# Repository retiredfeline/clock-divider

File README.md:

# Small clock divider board

These are the Kicad design files for a CD4060 based [small clock divider](https://hackaday.io/project/202239-small-clock-divider).

## Notes

A crystal (up to about 1.5 MHz) can be used, or an external clock source can be connected. A solder jumper enables the latter.

One of the divisor outputs can be routed with a solder jumper to drive the output transistor which is open collector.

## Authors

* **Ken Yap**

## License

See the [LICENSE](LICENSE.md) file for license rights and limitations (MIT).

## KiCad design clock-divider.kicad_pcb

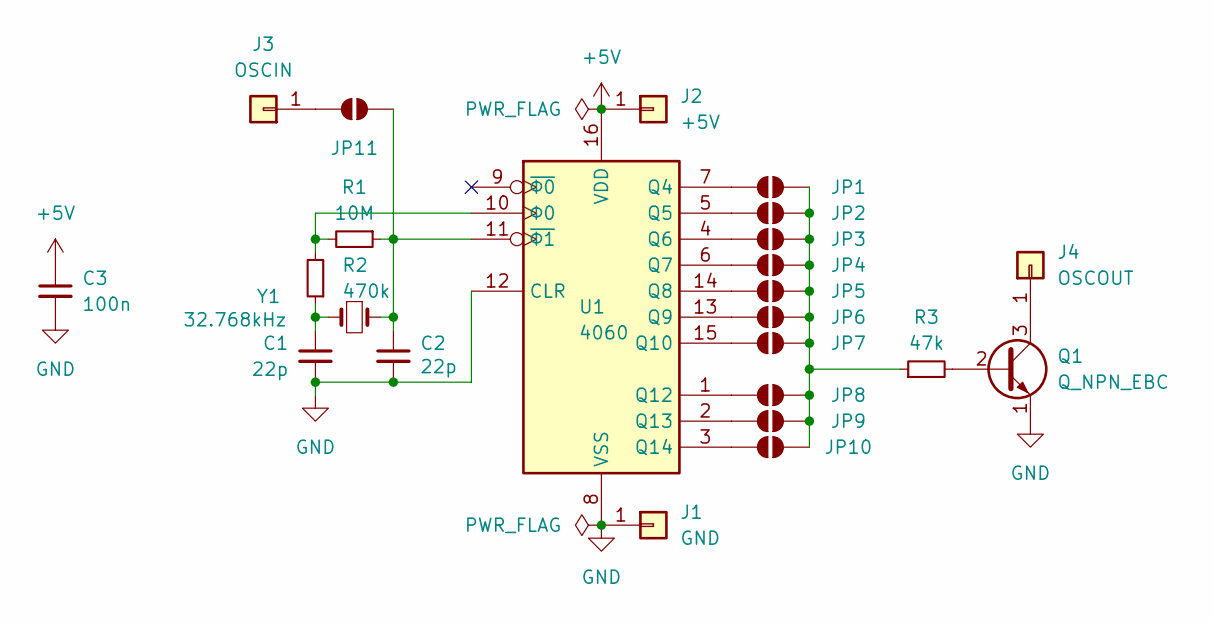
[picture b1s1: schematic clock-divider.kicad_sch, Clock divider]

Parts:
C1, C2: 22p; C_Disc_D3.0mm_W1.6mm_P2.50mm
C3: 100n; C_Disc_D3.0mm_W1.6mm_P2.50mm
J1: GND; SolderWire-0.1sqmm_1x01_D0.4mm_OD1mm
J2: +5V; SolderWire-0.1sqmm_1x01_D0.4mm_OD1mm
J3: OSCIN; SolderWire-0.1sqmm_1x01_D0.4mm_OD1mm
J4: OSCOUT; SolderWire-0.1sqmm_1x01_D0.4mm_OD1mm
JP1, JP2, JP3, JP4, JP5, JP6, JP7, JP8, JP9, JP10, JP11: SolderJumper_2_Open; SolderJumper-2_P1.3mm_Open_TrianglePad1.0x1.5mm
Q1: Q_NPN_EBC; TO-92L_Inline_Wide
R1: 10M; R_Axial_DIN0309_L9.0mm_D3.2mm_P2.54mm_Vertical
R2: 470k; R_Axial_DIN0309_L9.0mm_D3.2mm_P2.54mm_Vertical
R3: 47k; R_Axial_DIN0309_L9.0mm_D3.2mm_P2.54mm_Vertical
U1: 4060; DIP-16_W7.62mm
Y1: 32.768kHz; Crystal_C38-LF_D3.0mm_L8.0mm_Vertical_Extra_Pad

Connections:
+5V: C3.1, J2.1, U1.16 (VDD)
GND: C1.2, C2.2, C3.2, J1.1, Q1.1 (E), U1.8 (VSS), U1.12 (CLR)
unnamed: C1.1, R2.1, Y1.2
unnamed: J3.1, JP11.1 (A)
unnamed: J4.1, Q1.3 (C)
unnamed: JP1.1 (A), U1.7 (Q4)
unnamed: JP1.2 (B), JP2.2 (B), JP3.2 (B), JP4.2 (B), JP5.2 (B), JP6.2 (B), JP7.2 (B), JP8.2 (B), JP9.2 (B), JP10.2 (B), R3.1
unnamed: JP2.1 (A), U1.5 (Q5)
unnamed: JP3.1 (A), U1.4 (Q6)
unnamed: JP4.1 (A), U1.6 (Q7)
unnamed: JP5.1 (A), U1.14 (Q8)
unnamed: JP6.1 (A), U1.13 (Q9)
unnamed: JP7.1 (A), U1.15 (Q10)
unnamed: JP8.1 (A), U1.1 (Q12)
unnamed: JP9.1 (A), U1.2 (Q13)
unnamed: JP10.1 (A), U1.3 (Q14)
unnamed: C2.1, JP11.2 (B), R1.1, U1.11 (~Φ1), Y1.1
unnamed: Q1.2 (B), R3.2
unnamed: R1.2, R2.2, U1.10 (Φ0)

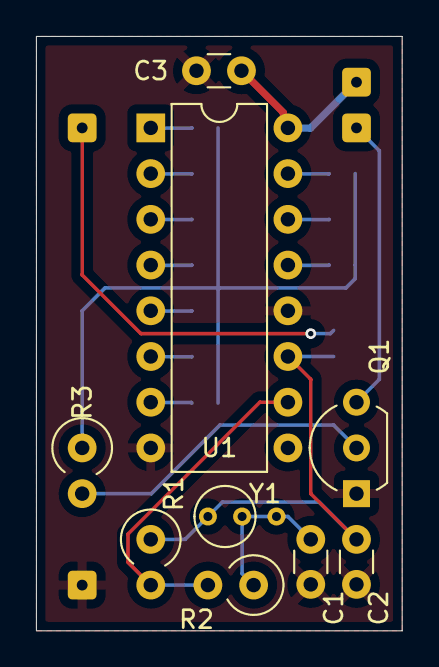
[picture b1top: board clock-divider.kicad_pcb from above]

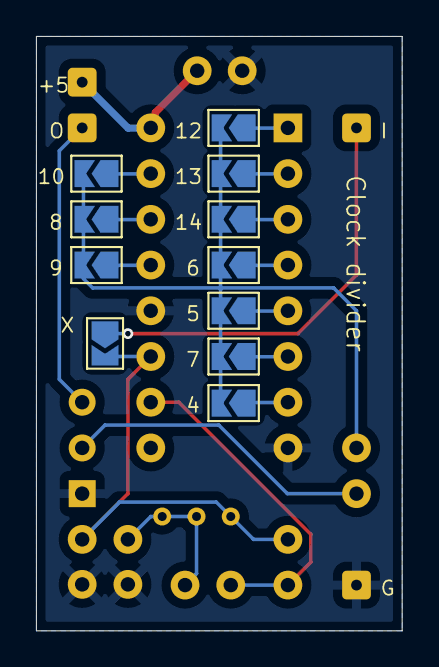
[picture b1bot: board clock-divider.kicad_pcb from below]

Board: 2 copper layers, 20.3 x 33.0 mm, 24 parts (11 on the bottom side), 19 nets.

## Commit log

2025-04-16 Use copyright symbol
